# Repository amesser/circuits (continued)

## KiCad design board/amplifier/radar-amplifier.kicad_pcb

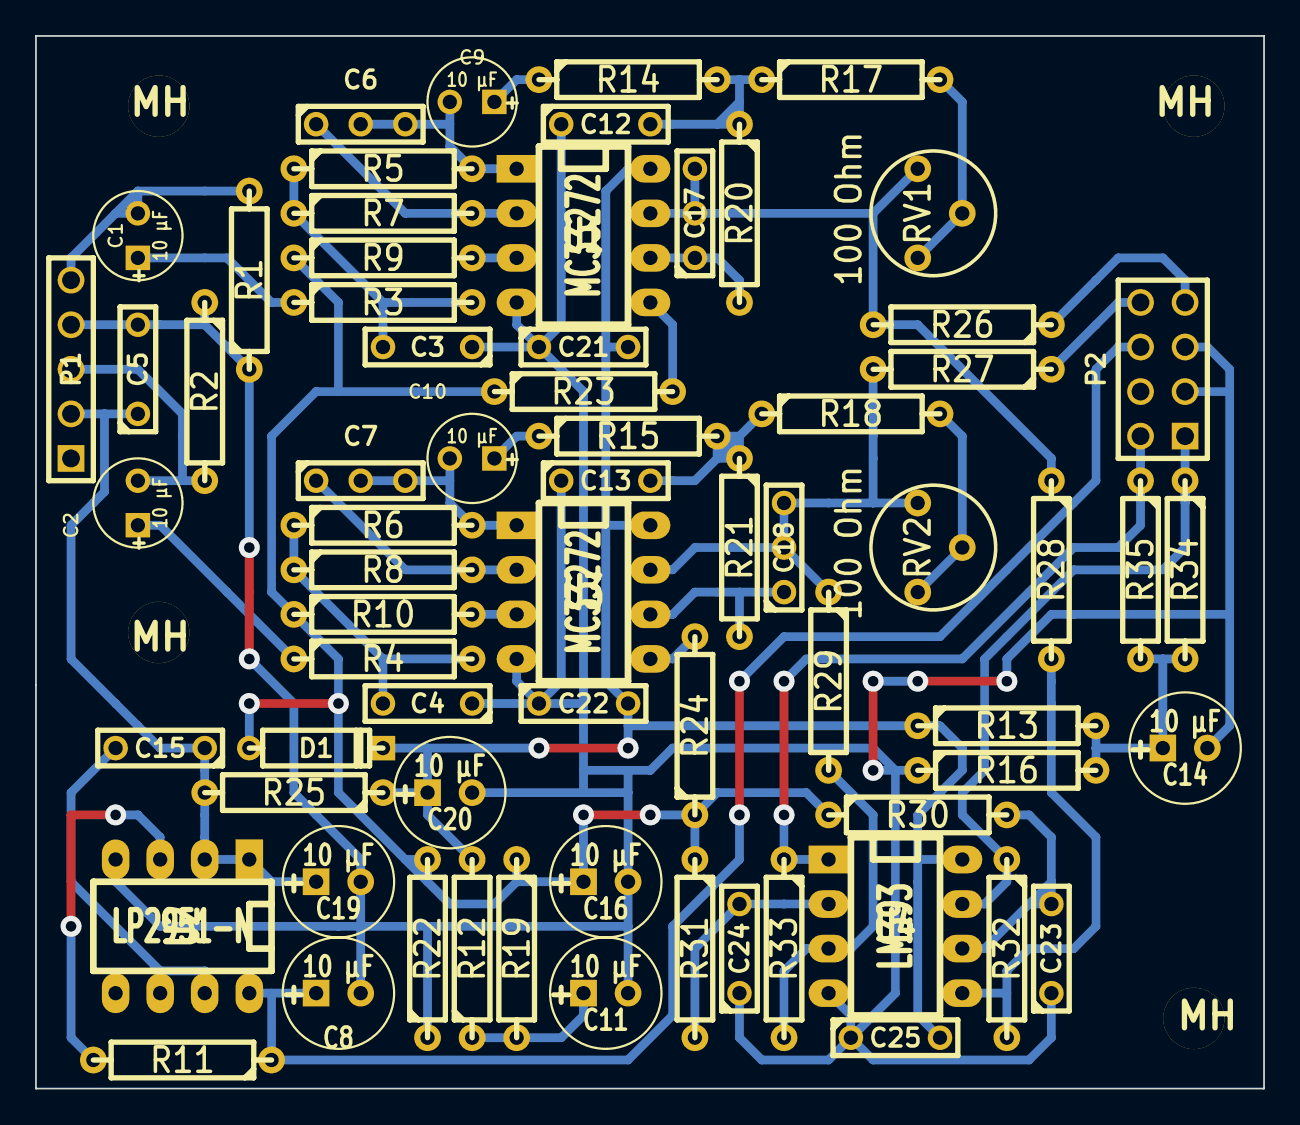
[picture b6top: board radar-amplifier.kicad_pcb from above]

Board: 2 copper layers, 70.0 x 60.0 mm, 73 parts (0 on the bottom side), 41 nets.

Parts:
C1, C2, C9, C10: 10 µF; C1V5
C3, C4, C15: 47 nF; C2
C5, C21, C22, C23, C24, C25: 100 nF; C2
C6, C7, C17, C18: 100 pF; C1-1
C8, C11, C14, C16, C19, C20: 10 µF; C1V7
C12, C13: 68 nF; C2
D1: DIODE; D3
MH: MountingHole_3-5mm_RevA_Date21Jun2010
MH#2, MH#3, MH#4: MountingHole_3-5mm_RevA_Date21Jun2010
P1: CONN_5; PIN_ARRAY_5x1
P2: CONN_4X2; pin_array_4x2
R1, R2, R12, R19, R22: 5.6 kOhm; R4
R3, R4, R14, R15: 120 Ohm; R4
R5, R6, R9, R10, R17, R18, R23, R24, R34, R35: 12 kOhm; R4
R7, R8, R16, R28, R29: 1.8 kOhm; R4
R11, R32, R33: 180 kOhm; R4
R13, R20, R21: 1 kOhm; R4
R25, R26, R27, R30, R31: 100 Ohm; R4
RV1, RV2: 100 Ohm; RV2
U1, U3: MC33272; DIP-8__300_ELL
U2: LP2951-N; DIP-8__300_ELL
U4: LM393; DIP-8__300_ELL

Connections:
+5V: C20.1, C21.2, C22.2, C25.2, D1.2, R12.2, R13.1, R25.1, U1.8, U3.8, U4.8
/CMP_I: P2.1, R32.1, R34.1, U4.7
/CMP_Q: P2.2, R33.1, R35.1, U4.1
/IN_I: C1.2, P1.5, R1.2
/IN_Q: C2.2, P1.3, R2.2
/OUT_I: P2.7, R26.1
/OUT_Q: P2.8, R27.1
/SHUTDOWN: P2.4, R11.2, U2.3
/Vref: C14.1, R13.2, R16.2, R34.2, R35.2
/Vref2: C16.1, D1.1, R9.1, R10.1, R19.1, R22.2, R23.1, R24.1, R30.1, R31.1
/Vsupply: C8.1, P2.6, R11.1, U2.8
/Vsupradar: C5.1, C15.1, C19.1, P1.2, R25.2, U2.1, U2.2
GND: C3.1, C4.1, C5.2, C8.2, C11.2, C12.1, C13.1, C14.2, C16.2, C19.2, C20.2, C21.1, C22.1, C23.1, C24.1, C25.1, P1.4, P2.3, P2.5, R1.1, R2.1, R16.1, R22.1, U1.4, U2.4, U3.4, U4.4
unnamed: R10.2, U3.3
unnamed: C18.2, R27.2, R29.1, RV2.1, U3.7
unnamed: R24.2, U3.5
unnamed: C18.1, R21.2, U3.6
unnamed: C13.2, R15.2, R18.1, R21.1
unnamed: C7.2, C10.2, R6.2, U3.1
unnamed: C10.1, R15.1
unnamed: C2.1, R4.1
unnamed: C7.1, R8.2, U3.2
unnamed: C4.2, R4.2, R6.1, R8.1
unnamed: C24.2, R31.2, U4.2
unnamed: R29.2, R33.2, U4.3
unnamed: C23.2, R30.2, U4.6
unnamed: R28.2, R32.2, U4.5
unnamed: R18.2, RV2.2, RV2.3
unnamed: C3.2, R3.2, R5.1, R7.1
unnamed: C6.2, C9.2, R5.2, U1.1
unnamed: R17.2, RV1.2, RV1.3
unnamed: C9.1, R14.1
unnamed: R23.2, U1.5
unnamed: C17.2, R26.2, R28.1, RV1.1, U1.7
unnamed: C17.1, R20.2, U1.6
unnamed: C12.2, R14.2, R17.1, R20.1
unnamed: R9.2, U1.3
unnamed: C1.1, R3.1
unnamed: C6.1, R7.2, U1.2
unnamed: C15.2, U2.6, U2.7
unnamed: C11.1, R12.1, R19.2

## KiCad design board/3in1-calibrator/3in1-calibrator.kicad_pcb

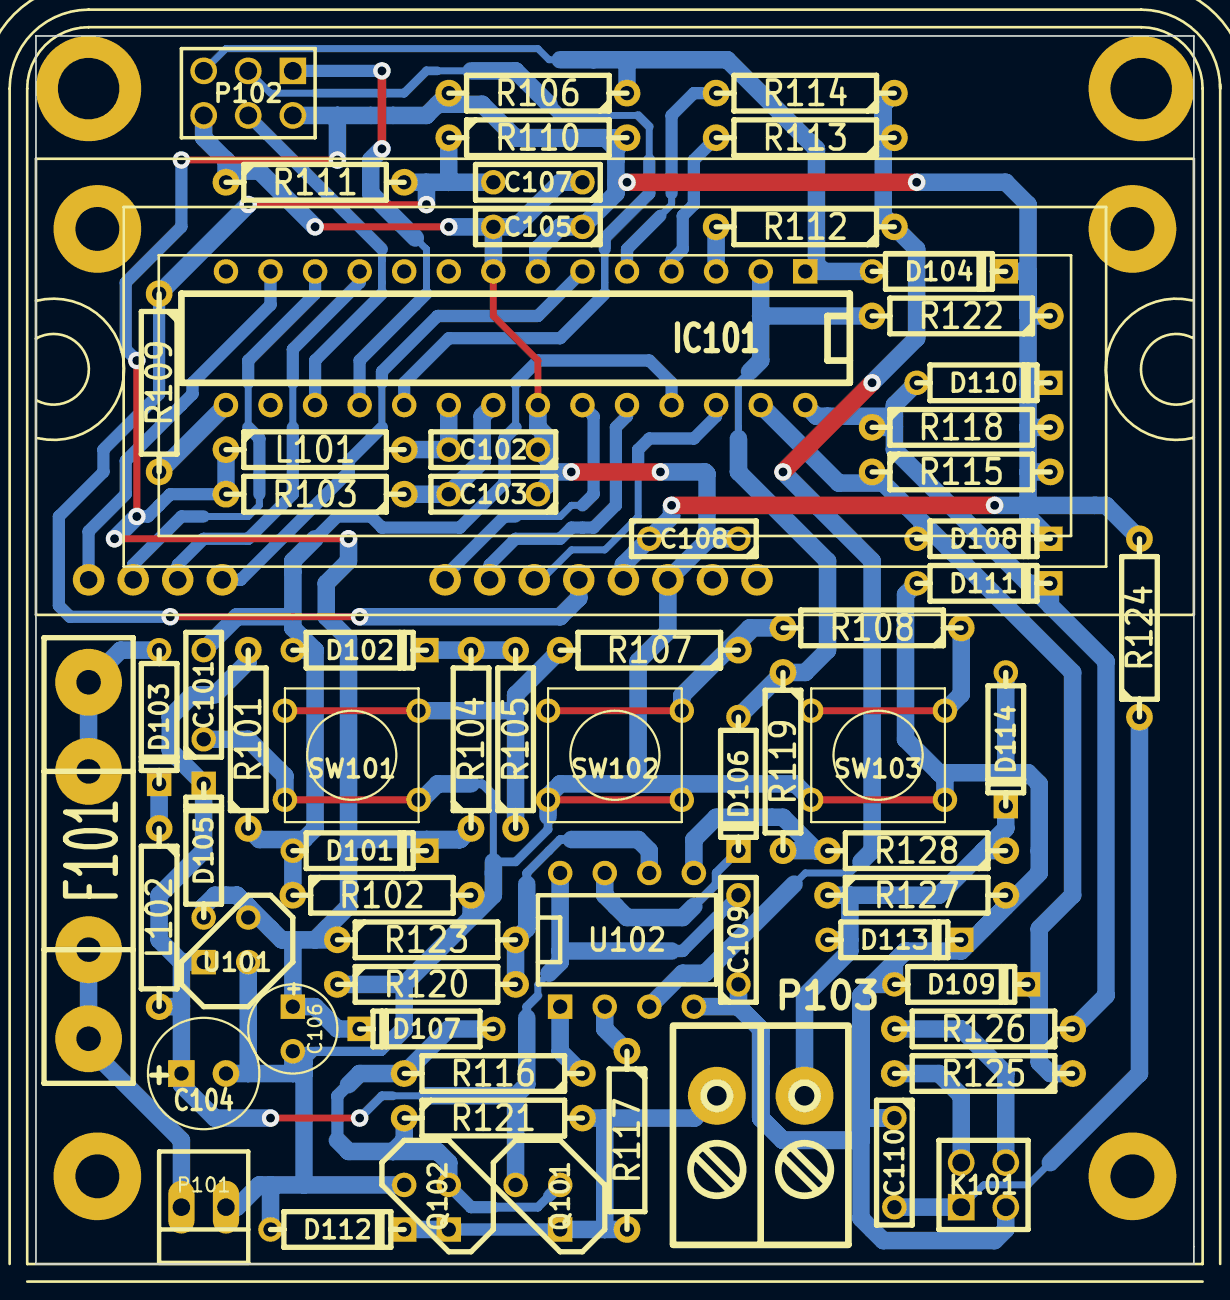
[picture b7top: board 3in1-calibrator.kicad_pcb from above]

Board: 2 copper layers, 66.0 x 70.0 mm, 69 parts (0 on the bottom side), 44 nets.

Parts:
C101, C102, C103, C105, C107, C108, C109, C110: C; C2
C104: 1u; C1V7
C106: 3.3 µF / 6.7 V; C1V5
D101, D102, D103, D104, D105, D106, D107, D108, D109, D110, D111, D112, D113, D114: DIODE; D3
DS101: LCM-S01602DTR; lumex_LCM-S01602DTR_4bit
F101: FUSE; FUSE5-20
IC101: ATMEGA8-P; DIP-28__300
K101: XLR4; PIN_ARRAY_2X2
L101, L102: 10 µH; R4
P101: CONN_2; PINHEAD1-2
P102: ISP; pin_array_3x2
P103: CONN_2; RIACON_007-2
Q101: NPN; TO92
Q102: PNP; TO92
R101, R123: 100 kOhm; R4
R102, R119: 47 kOhm; R4
R103, R104, R109, R111, R114, R115, R118, R120, R121, R122: 3.3 kOhm; R4
R105, R107, R108, R116, R125, R126, R127, R128: 68 Ohm; R4
R106, R110, R112, R113: 10 kOhm; R4
R117: 47k; R4
R124: 1 Ohm; R4
SW101, SW102, SW103: SW_PUSH_SMALL
U101: LP2950-N; TO92-123
U102: LM358; DIP-8__300
kemo_g02b: VAL**; kemo_g02b

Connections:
+5V: C105.1, C106.1, C108.2, D101.2, D104.2, D105.1, D107.2, D108.2, D110.2, DS101.2, IC101.7, L101.1, P102.2, R103.2, R104.1, R106.2, R110.2, R115.2, R118.2, R122.1, R123.1, R124.2, U101.1
/#RESET: D104.1, IC101.1, P102.5, R106.1
/KEYBOARD: C101.2, D101.1, D102.1, IC101.25, R101.1, R102.1
/LCD_CONTRAST_PWM: IC101.15, R109.2
/MISO: IC101.18, P102.1
/MOSI: IC101.17, P102.4
/SCK: IC101.19, P102.3
/SCL: D110.1, D111.2, IC101.28, R118.1, R126.1
/SDA: D108.1, D109.2, IC101.27, R115.1, R125.1
/SENSOR_RX: D106.1, IC101.2, R119.1, R122.2
/SENSOR_TX_A: IC101.3, R112.2
/SENSOR_TX_B: IC101.4, R113.2
/SENSOR_TX_C: IC101.5, R114.2
/Vsupply: C104.1, C109.2, D105.2, L102.2, Q101.3, R101.2, U101.3, U102.8
GND: C101.1, C102.1, C103.1, C104.2, C105.2, C106.2, C107.1, C108.1, C109.1, C110.1, D109.1, D111.1, D112.1, D113.2, D114.1, DS101.1, IC101.8, IC101.22, K101.3, P101.1, P102.6, Q102.3, R102.2, R111.1, R120.1, R127.2, SW101.1, SW102.1, SW103.1, U101.2, U102.4
unnamed: C110.2, K101.1, R124.1
unnamed: K101.2, R125.2
unnamed: K101.4, R126.2
unnamed: D106.2, U102.7
unnamed: D107.1, Q101.2, Q102.2, R116.2, R121.1
unnamed: R119.2, R128.2, U102.5
unnamed: D113.1, D114.2, P103.2, R127.1, R128.1
unnamed: R116.1, U102.1
unnamed: R117.1, U102.2
unnamed: R105.1, R107.2, SW101.2
unnamed: D102.2, R104.2, R105.2
unnamed: R107.1, R108.2, SW102.2
unnamed: R108.1, SW103.2
unnamed: DS101.4, IC101.26
unnamed: DS101.5, IC101.24
unnamed: R112.1, R113.1, R114.1, U102.3
unnamed: D112.2, P103.1, Q101.1, Q102.1, R117.2, R121.2
unnamed: R120.2, R123.2, U102.6
unnamed: D103.1, F101.2
unnamed: D103.2, L102.1
unnamed: F101.1, P101.2
unnamed: DS101.13, IC101.12
unnamed: DS101.11, IC101.6
unnamed: DS101.12, IC101.11
unnamed: DS101.14, IC101.13
unnamed: C107.2, DS101.3, R109.1, R110.1, R111.2
unnamed: DS101.6, IC101.23
unnamed: C103.2, IC101.21, R103.1
unnamed: C102.2, IC101.20, L101.2

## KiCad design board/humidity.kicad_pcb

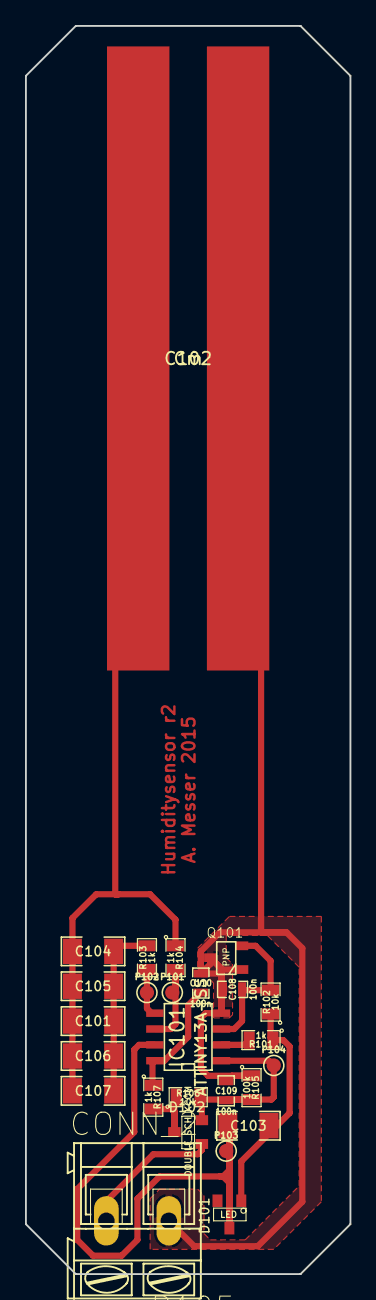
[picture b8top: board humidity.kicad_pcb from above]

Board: 2 copper layers, 26.0 x 100.0 mm, 26 parts (0 on the bottom side), 13 nets.

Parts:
C101, C103, C104, C105, C106, C107: 2n2 NP0; SM1206
C102: Cm; capsensor_5x50
C108, C109, C110: 100n; SM0603_Capa
D101: LED; SOT23-SPECIAL
D102: DOUBLE_SCH_KCOM; SOT23-SPECIAL
IC101: ATTINY13A-SS; SO8E
P101, P102, P103, P104: TST; PINTST
P105: CONN_2; AK300-2
Q101: PNP; SOT23_INV
R101, R103, R104, R107: 1k; SM0805
R102, R106: 10k; SM0805
R105: 100k; SM0805

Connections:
GND: C102.2, C108.2, C109.2, C110.2, IC101.4, P105.1, Q101.2, Q101.3, R105.1
unnamed: C103.1, D101.1, R101.1, R102.1
unnamed: IC101.2, R101.2
unnamed: C108.1, IC101.3, Q101.1, R102.2
unnamed: D102.1, P105.2
unnamed: C109.1, D102.3, IC101.1, P104.1, R105.2, R106.2
unnamed: C110.1, IC101.8, R107.1
unnamed: IC101.5, P102.1, R103.1
unnamed: IC101.6, P101.1, R104.2
unnamed: C103.2, D101.2, IC101.7, P103.1
unnamed: C101.2, C104.2, C105.2, C106.2, C107.2, R103.2
unnamed: C101.1, C102.1, C104.1, C105.1, C106.1, C107.1, R104.1
VCC: D102.2, R106.1, R107.2

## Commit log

2012-09-05 bench-power-supply: Initial circuit.
2013-01-30 Initial board and firmware version.
2013-02-05 Add Configuration for 1ms and 4 channels.
2013-02-05 Create .gitignore.
2013-02-05 Update to newest ecpp.
2013-02-05 Add calibration data block.
2013-02-05 Rework of major parts.
2013-02-05 Rework of analysis script.
2013-02-12 [Tool] Add configuration generation.
2013-02-24 Circuit Update
    * Assigned part values
    * Created SPICE simulation for Low-Pass Filter
2013-03-09 Schematic & Board Update.
2013-03-09 Update Python Tool.
2013-03-18 Update ecpp external.
2013-08-01 Implement numpy expressions for data tool.
2013-08-14 Add kicadlib externals.
2013-08-14 Readme file changes.
2013-08-14 Add board and schematic.
2013-08-14 Add spice simulation files.
2013-10-01 Prepared firmware directory structure
2013-12-19 Update to newest ecpp
2013-12-19 Schematics properties update
2013-12-19 First firmware version with basic functions
2013-12-19 Readme update and cleanup
2013-12-23 Code size optimizations.
2013-12-23 Support custom characters.
2014-01-19 Initial circuit work
2014-01-19 Finished analog frontend
2014-01-19 Analog frontend rework
    - remove unneeded components
    - rework 100db stage
2014-01-19 Initial Version of circuit
    - add power supply for 9 to 15v input
    - add atmega8 and support peripherals
    - add display connect circuitry
2014-01-21 circuit work
    - fix some issues in schematic
    - assigned footprints
2014-01-21 Readme update
2014-01-23 Initial layout work
    - layout first opamp stage
2014-01-25 Finish pcb layout
2014-01-26 Add mount holes to pcb
2014-03-12 Basic firmware implementation for tests
    - with 128 point dft
    - waveform and dft output to display
2014-03-15 Improve DFT algorithm and Graphicws output.
2014-05-21 Initial directory structure
2014-06-14 Start experiments with gnuradio
2014-07-23 Add Readme File
2014-07-23 Some initial work on python based dab decoder
2014-07-24 Add Frame Start detection
2014-07-29 Extend test script by fft
2014-07-31 Playing with sync and phase
2014-08-05 Tool Update
    * improve Frequency Correction
    * add OFDM Channel Selection
2014-08-07 Add depunctuation code
2014-08-12 Start with Viterby Decoder
    * Some work on Hard-Decision Viterby Decoder
    * Fixed several typos
2014-08-26 Simulation
    * modularize convolution decoder
2014-08-28 Simmulation
    * add viterby decoder
2014-09-02 Simulation
    * vectorize convolution encoder
2014-09-02 Simulation
    * add puncturing/depuncturing
    * fix hamming distance calculation
2014-09-09 Simulation
    * add soft decision viterby
2014-09-09 Simulation
    * use modules in test script
2014-09-11 Simulation
    * fix sign error in dqpsk demodulation
2014-09-11 Simulation
    * optimize average calculation
2014-09-11 Simulation
    * improve frequency correction
2014-09-24 Initial Commit
    * create circuit and pcb
    * add readme file
2014-09-24 Simulation
    * fix phase jump in frequency correction
    * use squared distance in viterby decoding
    * improve frequency correction
    * initial work on fic decoding
2014-09-24 Misc
    * update gitignore
2014-10-07 Simulation
    * some work on fic/fib decoding
    * bugfix for fic data storing
2014-10-22 Create initial hardware
    * create initial version of schematic
    * create initial version of pcb layout
2014-10-22 Initial Test Firmware
    * create a initial firmware displaying the ADC Readout
    of the first channel.
2014-10-22 Add Eclipse project files
2014-10-23 Extend firmware
    * encapsulate in classes
    * automatic calculation of shift bitmasks from pin numbers
2014-10-28 Continue implementation of simulation
    * create arbitrary crc function
    * implement dab+ superframe decoder
2014-11-06 Simulation
    * Add Reed Solomon Correction to dab data
2014-11-30 Add Kicad Submodule
2014-11-30 Initialrevision of Power Stage Circuit
2014-11-30 Finish initial revision of Schematic
2014-12-12 Finish schematic and assign footprints
2014-12-15 Finished Schematic and PCB
2015-01-01 Workaround segmentation fault of Kicad
    * Slightly increase Mask-Pad Offset to work around
    segementation fault when exporting gerber front mask
2015-01-06 Finish rs decoding simulation
2015-02-05 Some initial work to benchmark cortex-m4
2015-02-05 Code Cleanup
2015-02-05 Benchmark - Activate PLL as SysClock
2015-02-13 Initial Version of Firmware
2015-02-13 Add Readme
2015-02-13 add schematic
2015-02-13 Fix wrong diode
2015-02-13 Fix missing connection
2015-02-16 Fix wrong connections of PWM and ADC
2015-02-18 Add python script to convert from RS232 to lirc
2015-02-18 Setup git ignore
2015-03-01 Some initial work on firmware
2015-03-01 Fix ecpp external
2015-03-11 Fix ADC issues and Buck Startup
2015-03-24 Initial firmware version without MPPT
2015-03-25 Add current ramp for balancing mode
2015-03-31 Some initial work on MPP Tracking
2015-04-01 Fix several errors and improve MPPT tracking
2015-04-02 Rework Tracking algorithm.
2015-04-10 Improve temp compensation & statemachines
2015-04-16 Some initial work on dab-player application
2015-04-21 Move PT1 filter to ecpp
2015-04-21 Implement frequency correction & Channel Mapping
2015-05-14 Initial Sensor and Firmware
2015-05-14 Fix baud rate detection. use AC for Sensor
2015-05-19 Initial Revision of Controller schematic
2015-05-19 Fix problem with timer
2015-05-20 Initial revision of PCB
2015-06-04 Fix nterchanges RESET and CS pin of display
2015-06-04 Some initial work on controller firmware
2015-06-05 Implement Font handling for LCD
2015-06-07 Initial version of controller software without sensor
2015-07-05 Extend Sensor Firmware with Calibration
2015-07-08 Initialize calibration eeprom with default values
2015-07-12 Optimize sensor code
2015-07-19 Fix several bugs in sensor firmware
2015-07-26 Some initial work on calibrator firmware
2015-07-27 Implement LCD Display for calibrator
2015-07-28 Add Timers and UART handling to calibrator firmware
2015-08-09 Implement reading of sensor with baud rate adaption
2015-08-10 Move uart handling into separate class
2015-08-16 Basic work on user interface for calibrator
2015-08-16 Fix various bugs in voltage modulation.
2015-08-17 Make supply voltage detection more robust.
2015-08-17 Fix wrong return type.
2015-08-24 Allow re-use of calibration handling
2015-08-24 Implement display of sensor values
2015-09-06 Structural rework
    - rework function pointer invocation
    - implement linear regression
    - implement sensor data statistics for calibration
2015-09-11 Some work on calibration statistics processing
2015-09-19 Major rework of calibrator firmware
    * improve ui usability
    * rework internal state handling
2015-09-23 Implement reference temperature measurement
    * implement TWI driver for ATMega 8
    * implement periodic temperature measurement
2015-09-30 Initial version of calibrator firmware
2015-10-17 Major rework for asynchronous lcd handling
2015-10-22 Add unit test for fitting algorithms
2015-10-26 Implement linear regression fit
2015-10-26 Change raw temp count range to 0 to 1023
2015-10-26 Initialize Min field of calibration parameters
2015-10-27 Fix LCD display issues
2015-10-27 Rework calibration fitting
2015-11-01 Various bugfixes
2015-11-19 Improve UART debugging
2015-11-19 Rework calibration data collection
2015-12-29 Structural rework of project
2016-01-02 Fix LCD driver issues
2016-01-03 Structural project rework
2016-02-07 Add 2-channel amplifier board
2016-02-07 Fix typo
2016-02-14 Some initial work for traffic counter
2016-03-28 Implement most parts of traffic counter firmware
2016-05-06 Initial revision of traffic counter board
2016-05-06 Implement diagnosis logging
2016-06-23 Improved frequency counter
2017-01-01 Initial schematic version
2017-01-07 Add termination resistors
2017-01-11 Cleanup schematic and assign remaining values.
2017-01-15 Finalize schematic rev 1
2017-01-19 Assign footprints
2017-01-22 Some initial layout work
2017-02-01 PCB layout work
2017-02-08 Layout work
2017-02-16 Save last pcb layout work
2017-02-26 Pre-design definitions
2017-03-01 Update design and symbols
2017-03-02 Add Cyclone V DDR3 ram interface
2017-03-07 Add FPGA - FX3 interface
2017-03-08 Add DDR3 termination
2017-03-12 Add clock generation and jtag.
2017-03-12 Missing files
2017-03-15 Initial schematic and vhdl eval code for ports
2017-03-19 Update evaluation vhdl code
2017-03-21 Update user port pinout
2017-03-22 Add VCCPD voltage generation and VCCIO_B4 voltage limiter
2017-03-23 Add USB3.0, SD-Card and additional connectors
2017-03-24 Replace MICROSD with additional pin header
2017-03-26 Add Power supply
2017-03-26 Calc Power supply & cleanup schematics
2017-03-28 Define decoupling cap requirements
2017-03-29 Finalize initial schematic
2017-05-11 Add project files
2017-05-12 Add photographs of pcb and sensor
2017-06-20 Review schematic and FPGA pin assignments
2017-07-17 Finalize footprint assignment
2017-07-31 Some initial DDR3 Ram routing
2017-08-13 Initial layout work
2017-08-18 Rework power supply and simplify some things
2017-08-23 Rework power supply
2017-09-12 Rework schematic
    - use better capacitors
    - drop several, probably unneeded components
    - make connectors PMOD compatible
2017-09-13 PCB Layout
2017-09-15 PCB Lacout work
2017-09-17 Further layout work
2017-09-24 Initial routing work for FX3 signals
2017-10-03 Some pcb layout work
2017-10-03 Fix input clock assignment for PLLs
2017-10-05 General circuit work
    - Change io power switch iv
    - reassign some user io pins to improve layout
    - escape route user io lines from fpga
2017-10-09 Inital routing for User IO Port C
2017-10-16 Finish initial fx3 fifo routing
2017-10-26 PCB routing
2017-11-02 PCB routing work
2017-11-21 Some DDR3 signal deskewing
2017-11-22 Finish initial layer 4 DDR3 deskew
2017-11-28 DDR3 layout work
2017-12-06 pcb layput work
2018-02-10 Fix improper handling of read timeout
2018-08-22 Initial version of schematic
2018-08-29 Review and finalize schematic
2018-09-13 Layout work for power stage
2018-09-20 Condense layout
2018-09-23 Finish first revision of layout
2018-09-26 Finalize & validate layout
2018-12-29 Initial hardware revision
2018-12-29 Add text & copyright notice
2018-12-29 Add meta information & reduce board size
2018-12-30 Finalization of hardware
2018-12-30 Add some documentation
2018-12-30 Introduce README file
2018-12-30 Prepare documentation frame
2019-01-03 Increase via size
2019-01-03 Fix areas in various places
2019-02-01 Update project file
2020-08-05 Document hardware issue with higher temperatures
